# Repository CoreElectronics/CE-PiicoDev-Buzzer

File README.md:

# PiicoDev® Buzzer Module

This is the repo for the Core Electronics [PiicoDev Buzzer Module](https://core-electronics.com.au/catalog/product/view/sku/CE08219).

[**Guides**](https://core-electronics.com.au/catalog/product/view/sku/CE08219#guides) for Micro:bit, Raspberry Pi and Pico

## License
This project is open source - please review the LICENSE.md file for further licensing information.

If you have any technical questions, or concerns about licensing, please contact technical support on the [Core Electronics forums](https://forum.core-electronics.com.au/).

# Attribution
C++ code firmware project is based off the [Qwiic Open Log](https://github.com/sparkfun/Qwiic_OpenLog) project by Sparkfun. It makes use of the register structure and i2c device drivers.

*\"PiicoDev\" and the PiicoDev logo are trademarks of Core Electronics Pty Ltd.*

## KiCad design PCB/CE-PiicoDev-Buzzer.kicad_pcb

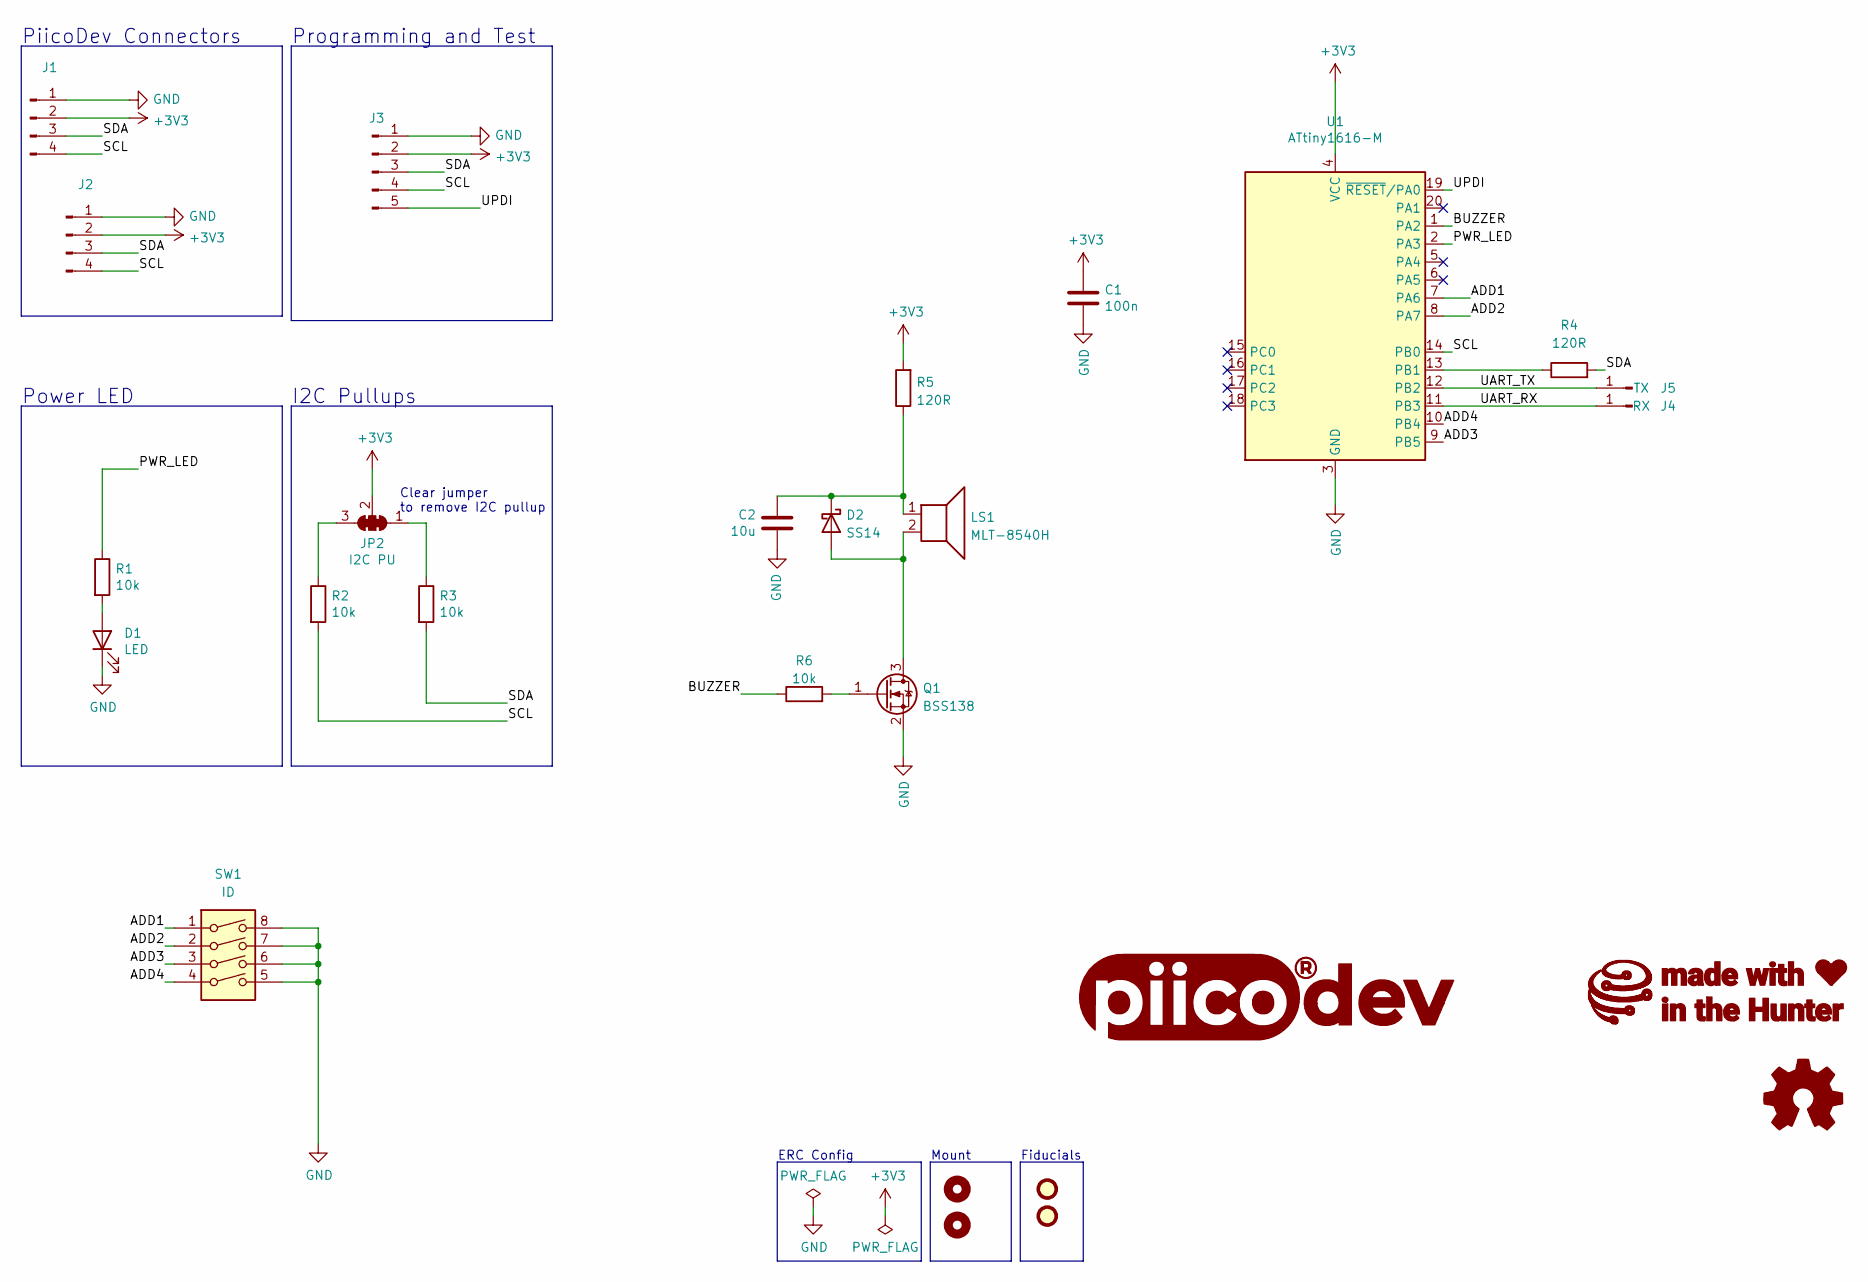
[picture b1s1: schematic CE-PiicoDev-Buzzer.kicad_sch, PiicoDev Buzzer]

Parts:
C1: 100n; C_0402_1005Metric
C2: 10u; C_0603_1608Metric
D1: LED; LED_0603_1608Metric
D2: SS14; D_SMA
FID1, FID2: Fiducial; Fiducial_1mm_Mask2mm_No_Courtyard
G1: LOGO_PiicoDev; piicodev_logo_14.2x3.4mm
G2: LOGO_CoreElectronics_no-text; CoreElectronics_logo_5mm_v2
G3: LOGO_made-with-love; piicodev_logo_14.2x3.4mm
H1, H2: MountingHole; MountingHole_2.7mm_M2.5_PadClearance_1.2
J1, J2: JST_SH_SM04B-SRSS-TB_1x04-1MP_P1.00mm_Horizontal
J3: Conn_01x05_Male; TestPoint_Pad_D1.0mm_x05_Pattern1
J4: RX; TestPoint_Pad_D1.5mm
J5: TX; TestPoint_Pad_D1.5mm
JP2: I2C PU; SolderJumper-3_P1.3mm_Closed_RoundedPad1.0x1.5mm_NumberLabe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
LOGO1: Logo_Open_Hardware_Small; oshw
LS1: MLT-8540H; CUI_CMT-8540S-SMT
Q1: BSS138; SOT-23
R1, R2, R3, R6: 10k; R_0402_1005Metric
R4, R5: 120R; R_0402_1005Metric
SW1: ID; SW_DIP_x04_Slide_CHS-04A1
U1: ATtiny1616-M; VQFN-20-1EP_3x3mm_P0.4mm_EP1.7x1.7mm

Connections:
+3V3: C1.1, J1.2, J2.2, J3.2, JP2.2 (C), R5.2, U1.4 (VCC)
/ADD1: SW1.1, U1.7 (PA6)
/ADD2: SW1.2, U1.8 (PA7)
/ADD3: SW1.3, U1.9 (PB5)
/ADD4: SW1.4, U1.10 (PB4)
/BUZZER: R6.1, U1.1 (PA2)
/PWR_LED: R1.1, U1.2 (PA3)
/SCL: J1.4, J2.4, J3.4, R2.2, U1.14 (PB0)
/SDA: J1.3, J2.3, J3.3, R3.2, R4.2
/UART_RX: J4.1, U1.11 (PB3)
/UART_TX: J5.1, U1.12 (PB2)
/UPDI: J3.5, U1.19 (~RESET/PA0)
GND: C1.2, C2.2, D1.1 (K), J1.1, J2.1, J3.1, Q1.2 (S), SW1.5, SW1.6, SW1.7, SW1.8, U1.3 (GND), U1.21 (GND)
unnamed: C2.1, D2.1 (K), LS1.1, R5.1
unnamed: D1.2 (A), R1.2
unnamed: D2.2 (A), LS1.2, Q1.3 (D)
unnamed: JP2.1 (A), R3.1
unnamed: JP2.3 (B), R2.1
unnamed: Q1.1 (G), R6.2
unnamed: R4.1, U1.13 (PB1)

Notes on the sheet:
Programming and Test
PiicoDev Connectors
I2C Pullups
Power LED
Mount
Clear jumper to remove I2C pullup
ERC Config
Fiducials

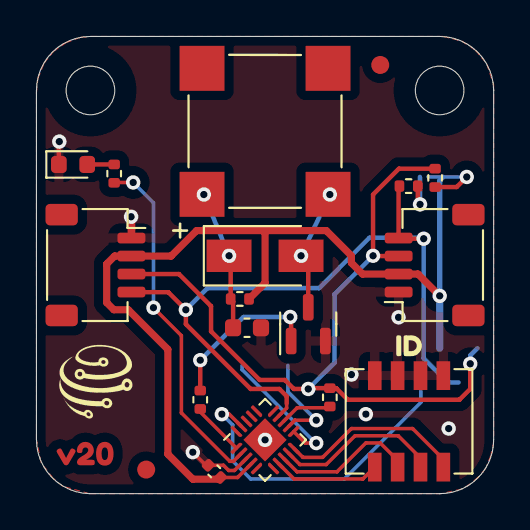
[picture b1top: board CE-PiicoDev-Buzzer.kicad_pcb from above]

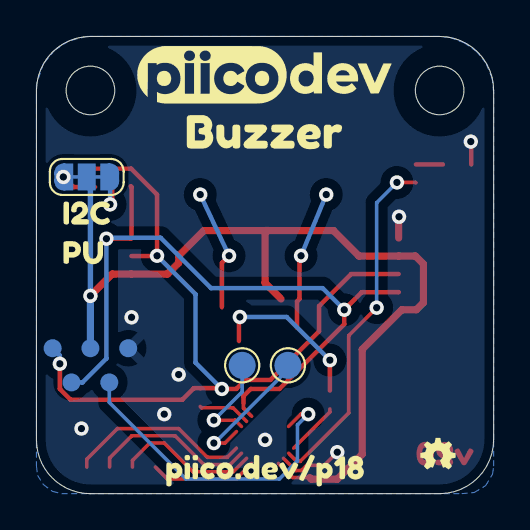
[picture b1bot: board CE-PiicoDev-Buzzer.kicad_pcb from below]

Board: 2 copper layers, 25.4 x 25.4 mm, 32 parts (9 on the bottom side), 20 nets.

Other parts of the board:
kibuzzard-63C9FEBD: G***; kibuzzard-63C9FEBD
kibuzzard-63C9FF03: G***; kibuzzard-63C9FF03
kibuzzard-63CA00A3: G***; kibuzzard-63CA00A3
kibuzzard-63883A97: G***; kibuzzard-63883A97
kibuzzard-6388073A: G***; kibuzzard-6388073A

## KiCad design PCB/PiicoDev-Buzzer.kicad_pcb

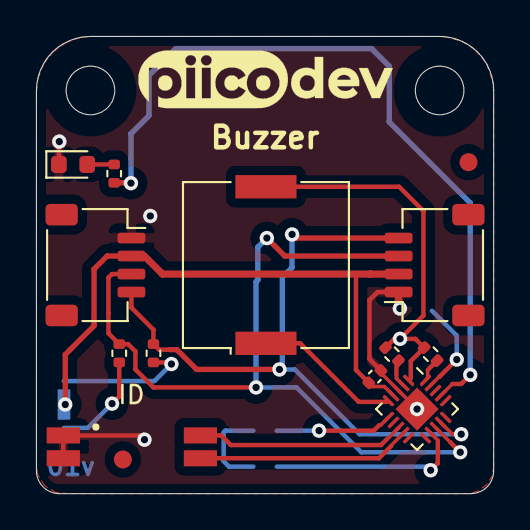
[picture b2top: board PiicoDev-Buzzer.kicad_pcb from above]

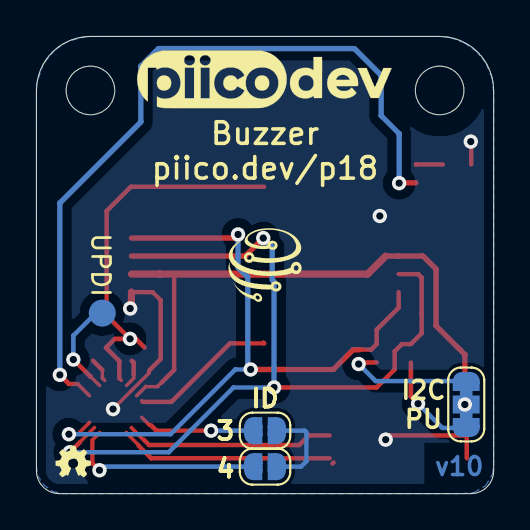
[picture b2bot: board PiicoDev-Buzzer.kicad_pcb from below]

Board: 2 copper layers, 25.4 x 25.4 mm, 23 parts (6 on the bottom side), 17 nets.

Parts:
C1: 100n; C_0402_1005Metric
D1: LED; LED_0603_1608Metric
FID1, FID2: Fiducial; Fiducial_1mm_Mask2mm
G1: LOGO_PiicoDev; piicodev_logo_14.2x3.4mm
G2: LOGO_CoreElectronics_no-text; CoreElectronics_logo_5mm_v2
G3: LOGO_made-with-love; piicodev_logo_14.2x3.4mm
H1, H2: MountingHole; MountingHole_2.7mm_M2.5_PadClearance_1.2
J1: JST_SH_SM04B-SRSS-TB_1x04-1MP_P1.00mm_Horizontal
J2: PiicoDev_Connector_with_UPDI
JP2: I2C PU; SolderJumper-3_P1.3mm_Closed_RoundedPad1.0x1.5mm_NumberLabe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
JP3, JP5: SolderJumper_2_Open; SolderJumper-2_P1.3mm_Open_RoundedPad1.0x1.5mm
LOGO1: Logo_Open_Hardware_Small; oshw
LS1: Speaker_Crystal; Buzzer_Murata_PKMCS0909E
R1, R2, R3: 10k; R_0402_1005Metric
R4: 4k7; R_0402_1005Metric
R5: 1k; R_0402_1005Metric
SW1: ADDR; SW_DIP_SPSTx02_Slide_DSHP
U1: ATtiny806; VQFN-20-1EP_3x3mm_P0.4mm_EP1.7x1.7mm

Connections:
+3V3: C1.1, J1.2, J2.2, JP2.2, U1.4
/ADD1: SW1.4, U1.8
/ADD2: SW1.3, U1.9
/ADD3: JP3.1, U1.6
/ADD4: JP5.1, U1.12
/BUZZ: LS1.1, U1.5
/BUZZ_1: R4.1, U1.2
/BUZZ_2: R5.1, U1.20
/BUZZ_3: LS1.2, R4.2, R5.2, U1.1
/PWR_LED: R1.1, U1.17
/SCL: J1.4, J2.4, R2.2, U1.14
/SDA: J1.3, J2.3, R3.2, U1.13
/UPDI: J2.5, U1.19
GND: C1.2, D1.1, J1.1, J2.1, JP3.2, JP5.2, SW1.1, SW1.2, U1.3, U1.21
unnamed: D1.2, R1.2
unnamed: JP2.1, R3.1
unnamed: JP2.3, R2.1

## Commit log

2022-02-01 Change R1 to 10k
2023-01-19 KiCad v5 -> v6
2023-01-20 provisional v20 design
2023-04-05 V20 (#1)
    * provisional v20 design
    * v20

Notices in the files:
PCB/CE-PiicoDev-Buzzer.kicad_sch:
License: CCASAv4.0 http://creativecommons.org/licenses/by-sa/4.0
